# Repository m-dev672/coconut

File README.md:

## Coconut
It's a keyboard which has 38 keys!</br>
You can use ANSI 104 layout keycaps for this keyboard.

## Used web site, software and library for this project.
1. http://www.keyboard-layout-editor.com/
2. https://kb.xyz.is/
3. https://msys.qmk.fm/
4. https://kbfirmware.com/
5. https://www.kicad.org/
6. https://github.com/g200kg/kicad-lib-arduino

## LICENCE

```
MIT License

Copyright (c) 2022 Koutarou Mori

Permission is hereby granted, free of charge, to any person obtaining a copy
of this software and associated documentation files (the "Software"), to deal
in the Software without restriction, including without limitation the rights
to use, copy, modify, merge, publish, distribute, sublicense, and/or sell
copies of the Software, and to permit persons to whom the Software is
furnished to do so, subject to the following conditions:

The above copyright notice and this permission notice shall be included in all
copies or substantial portions of the Software.

THE SOFTWARE IS PROVIDED "AS IS", WITHOUT WARRANTY OF ANY KIND, EXPRESS OR
IMPLIED, INCLUDING BUT NOT LIMITED TO THE WARRANTIES OF MERCHANTABILITY,
FITNESS FOR A PARTICULAR PURPOSE AND NONINFRINGEMENT. IN NO EVENT SHALL THE
AUTHORS OR COPYRIGHT HOLDERS BE LIABLE FOR ANY CLAIM, DAMAGES OR OTHER
LIABILITY, WHETHER IN AN ACTION OF CONTRACT, TORT OR OTHERWISE, ARISING FROM,
OUT OF OR IN CONNECTION WITH THE SOFTWARE OR THE USE OR OTHER DEALINGS IN THE
SOFTWARE.
```

This project was developped using a lot of software, etc.</br>
and I couldn't understand license of all.</br>
If there are any infringement, please contact me.

As shown above, this project is basically licensed under MIT license,</br>
but The files in /qmk-firmware and firmware.hex in releases page are licensed under GPL v3 license.

Sharing gerber_nonfree.zip in releases page is prohibited.

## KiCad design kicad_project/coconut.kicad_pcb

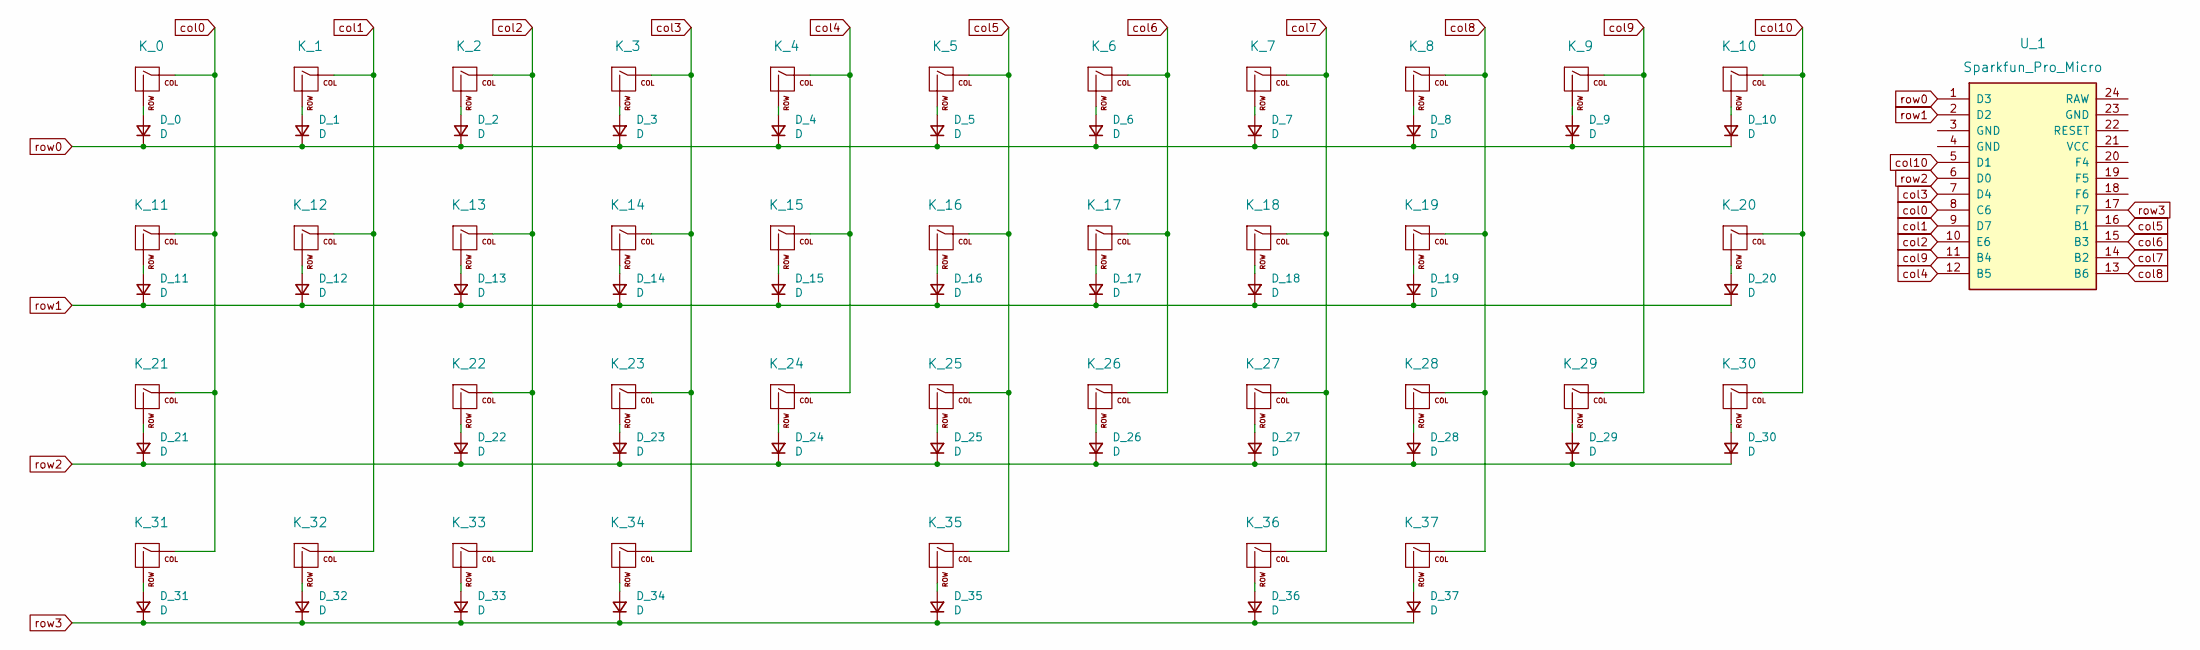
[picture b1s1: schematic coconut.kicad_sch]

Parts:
D_0, D_1, D_2, D_3, D_4, D_5, D_6, D_7, D_8, D_9, D_10, D_11, D_12, D_13, D_14, D_15, D_16, D_17, D_18, D_19, D_20, D_21, D_22, D_23, D_24, D_25, D_26, D_27, D_28, D_29, D_30, D_31, D_32, D_33, D_34, D_35, D_36, D_37: D; D_SOD-123
K_0, K_1, K_2, K_3, K_4, K_5, K_6, K_7, K_8, K_9, K_10, K_11, K_12, K_13, K_14, K_15, K_16, K_17, K_18, K_19, K_22, K_23, K_24, K_25, K_26, K_27, K_28, K_29, K_30, K_33, K_37: KEYSW; MXOnly-1U-NoLED
K_20: KEYSW; MXOnly-1.75U-NoLED
K_21: KEYSW; MXOnly-2U-NoLED
K_31, K_32, K_34, K_36: KEYSW; MXOnly-1.25U-NoLED
K_35: KEYSW; MXOnly-2.25U-NoLED
U_1: Sparkfun_Pro_Micro

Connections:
unnamed: D_0.2 (A), K_0.2 (ROW)
unnamed: D_1.2 (A), K_1.2 (ROW)
unnamed: D_2.2 (A), K_2.2 (ROW)
unnamed: D_3.2 (A), K_3.2 (ROW)
unnamed: D_4.2 (A), K_4.2 (ROW)
unnamed: D_5.2 (A), K_5.2 (ROW)
unnamed: D_6.2 (A), K_6.2 (ROW)
unnamed: D_7.2 (A), K_7.2 (ROW)
unnamed: D_8.2 (A), K_8.2 (ROW)
unnamed: D_9.2 (A), K_9.2 (ROW)
unnamed: D_10.2 (A), K_10.2 (ROW)
unnamed: D_11.2 (A), K_11.2 (ROW)
unnamed: D_12.2 (A), K_12.2 (ROW)
unnamed: D_13.2 (A), K_13.2 (ROW)
unnamed: D_14.2 (A), K_14.2 (ROW)
unnamed: D_15.2 (A), K_15.2 (ROW)
unnamed: D_16.2 (A), K_16.2 (ROW)
unnamed: D_17.2 (A), K_17.2 (ROW)
unnamed: D_18.2 (A), K_18.2 (ROW)
unnamed: D_19.2 (A), K_19.2 (ROW)
unnamed: D_20.2 (A), K_20.2 (ROW)
unnamed: D_21.2 (A), K_21.2 (ROW)
unnamed: D_22.2 (A), K_22.2 (ROW)
unnamed: D_23.2 (A), K_23.2 (ROW)
unnamed: D_24.2 (A), K_24.2 (ROW)
unnamed: D_25.2 (A), K_25.2 (ROW)
unnamed: D_26.2 (A), K_26.2 (ROW)
unnamed: D_27.2 (A), K_27.2 (ROW)
unnamed: D_28.2 (A), K_28.2 (ROW)
unnamed: D_29.2 (A), K_29.2 (ROW)
unnamed: D_30.2 (A), K_30.2 (ROW)
unnamed: D_31.2 (A), K_31.2 (ROW)
unnamed: D_32.2 (A), K_32.2 (ROW)
unnamed: D_33.2 (A), K_33.2 (ROW)
unnamed: D_34.2 (A), K_34.2 (ROW)
unnamed: D_35.2 (A), K_35.2 (ROW)
unnamed: D_36.2 (A), K_36.2 (ROW)
unnamed: D_37.2 (A), K_37.2 (ROW)
col0: K_0.1 (COL), K_11.1 (COL), K_21.1 (COL), K_31.1 (COL), U_1.8 (C6)
col1: K_1.1 (COL), K_12.1 (COL), K_32.1 (COL), U_1.9 (D7)
col2: K_2.1 (COL), K_13.1 (COL), K_22.1 (COL), K_33.1 (COL), U_1.10 (E6)
col3: K_3.1 (COL), K_14.1 (COL), K_23.1 (COL), K_34.1 (COL), U_1.7 (D4)
col4: K_4.1 (COL), K_15.1 (COL), K_24.1 (COL), U_1.12 (B5)
col5: K_5.1 (COL), K_16.1 (COL), K_25.1 (COL), K_35.1 (COL), U_1.16 (B1)
col6: K_6.1 (COL), K_17.1 (COL), K_26.1 (COL), U_1.15 (B3)
col7: K_7.1 (COL), K_18.1 (COL), K_27.1 (COL), K_36.1 (COL), U_1.14 (B2)
col8: K_8.1 (COL), K_19.1 (COL), K_28.1 (COL), K_37.1 (COL), U_1.13 (B6)
col9: K_9.1 (COL), K_29.1 (COL), U_1.11 (B4)
col10: K_10.1 (COL), K_20.1 (COL), K_30.1 (COL), U_1.5 (D1)
row0: D_0.1 (K), D_1.1 (K), D_2.1 (K), D_3.1 (K), D_4.1 (K), D_5.1 (K), D_6.1 (K), D_7.1 (K), D_8.1 (K), D_9.1 (K), D_10.1 (K), U_1.1 (D3)
row1: D_11.1 (K), D_12.1 (K), D_13.1 (K), D_14.1 (K), D_15.1 (K), D_16.1 (K), D_17.1 (K), D_18.1 (K), D_19.1 (K), D_20.1 (K), U_1.2 (D2)
row2: D_21.1 (K), D_22.1 (K), D_23.1 (K), D_24.1 (K), D_25.1 (K), D_26.1 (K), D_27.1 (K), D_28.1 (K), D_29.1 (K), D_30.1 (K), U_1.6 (D0)
row3: D_31.1 (K), D_32.1 (K), D_33.1 (K), D_34.1 (K), D_35.1 (K), D_36.1 (K), D_37.1 (K), U_1.17 (F7)

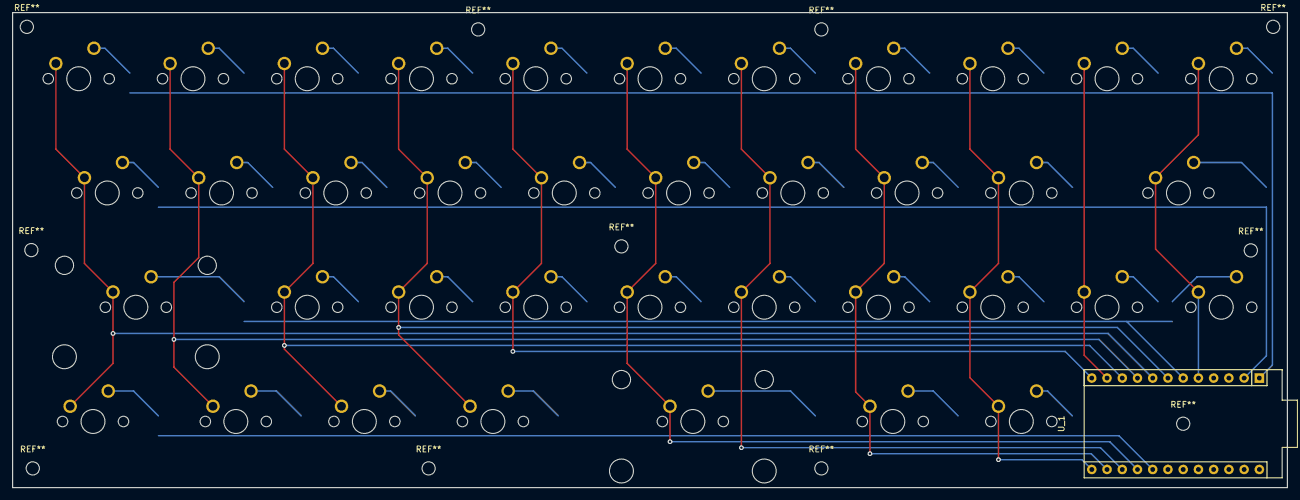
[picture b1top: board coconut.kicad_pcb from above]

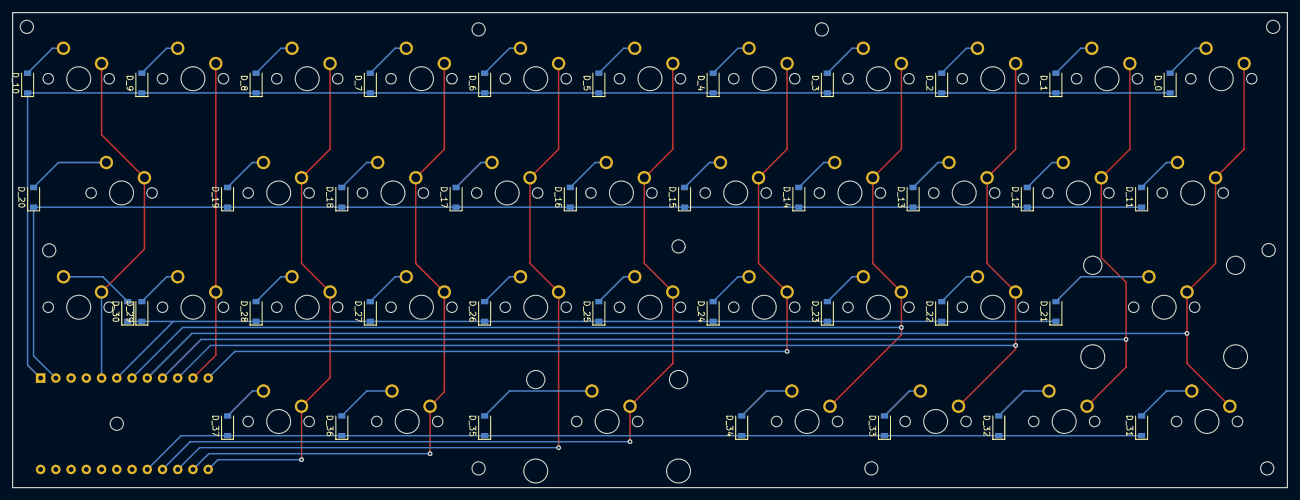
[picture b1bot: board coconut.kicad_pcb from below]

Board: 2 copper layers, 212.6 x 79.2 mm, 77 parts (38 on the bottom side), 53 nets.

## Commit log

2022-06-21 second commit
2022-06-21 change the layout
2022-06-21 fix mismatch
2022-06-21 update images
2022-06-21 add clearance
2022-06-23 fix holes
2022-06-23 fix pin assignments
